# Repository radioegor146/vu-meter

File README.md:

# vu-meter

Physical VU meter for use with rack audio equipment

Consists of:
- 1 processor board
- 4 indicator boards (2 boards per channel)

## Processor board

The processor board is a simple board with converter from balanced input to unbalanced with 
2 x CH32X035F7P6 MCU to convert from analog domain to digital for output to SPI for shift registers.

## Indicator board

This board consists of 5 74HC595D shift registers for 35 individual LEDs.

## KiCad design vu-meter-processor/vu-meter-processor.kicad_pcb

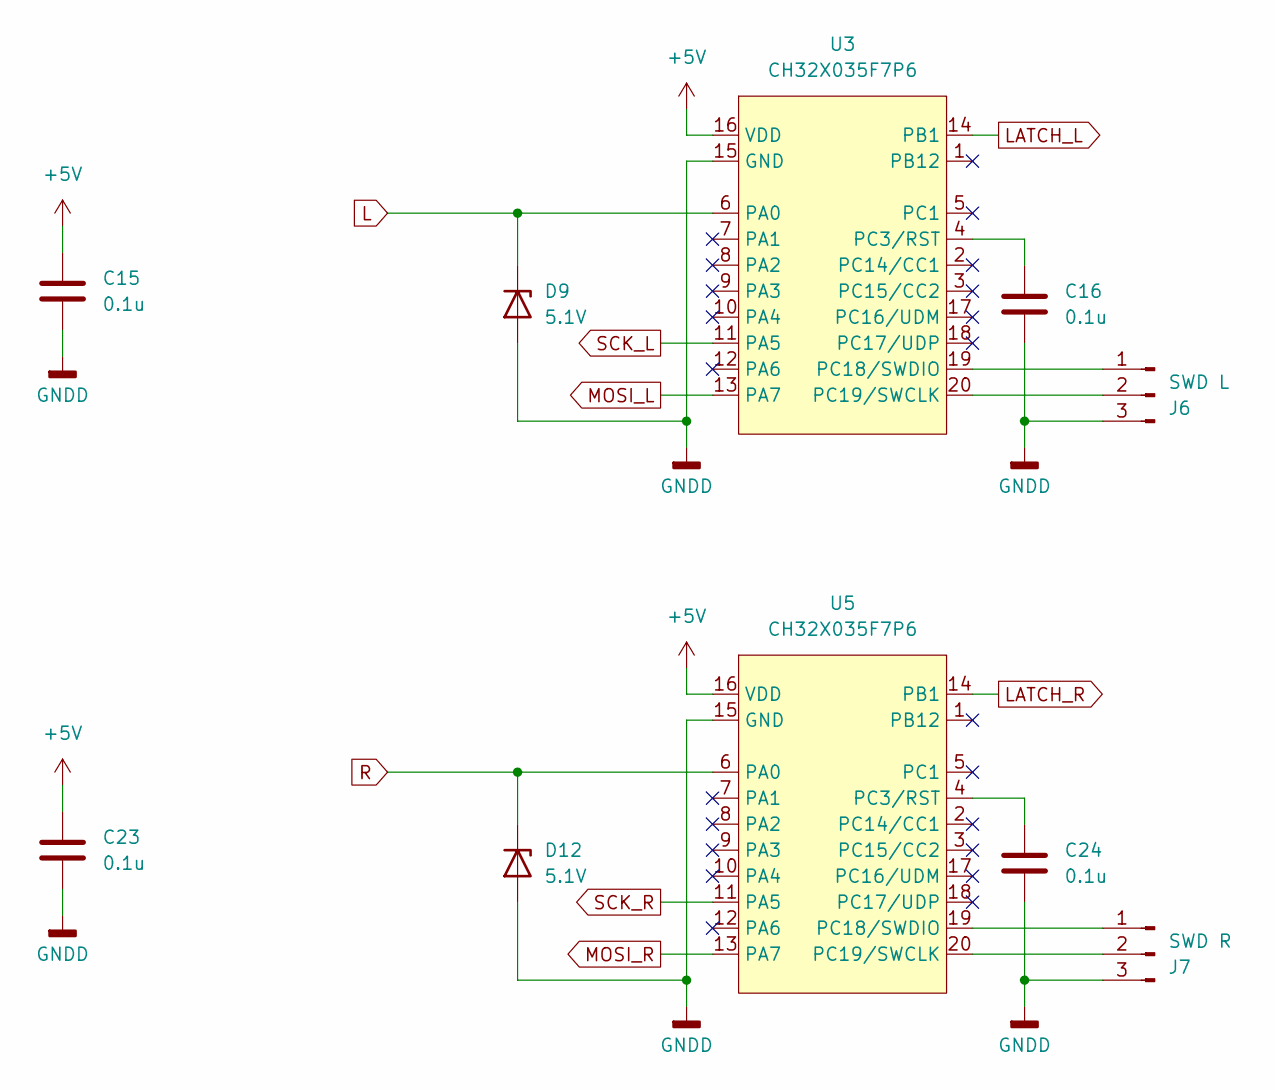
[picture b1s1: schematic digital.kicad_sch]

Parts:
C15, C16, C23, C24: 0.1u; C_0805_2012Metric
D9, D12: 5.1V; D_MiniMELF
J6: SWD L; PinHeader_1x03_P2.54mm_Vertical
J7: SWD R; PinHeader_1x03_P2.54mm_Vertical
U3, U5: CH32X035F7P6; TSSOP-20_4.4x6.5mm_P0.65mm

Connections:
+5V: C15.1, C23.1, U3.16 (VDD), U5.16 (VDD); also elsewhere on the board
GNDA: C15.2, C16.2, C23.2, C24.2, D9.2 (A), D12.2 (A), J6.3, J7.3, U3.15 (GND), U5.15 (GND); also elsewhere on the board
L: D9.1 (K), U3.6 (PA0); also elsewhere on the board
LATCH_L: U3.14 (PB1); also elsewhere on the board
LATCH_R: U5.14 (PB1); also elsewhere on the board
MOSI_L: U3.13 (PA7); also elsewhere on the board
MOSI_R: U5.13 (PA7); also elsewhere on the board
unnamed: J6.1, U3.19 (PC18/SWDIO)
unnamed: J6.2, U3.20 (PC19/SWCLK)
unnamed: J7.1, U5.19 (PC18/SWDIO)
unnamed: J7.2, U5.20 (PC19/SWCLK)
unnamed: C16.1, U3.4 (PC3/RST)
unnamed: C24.1, U5.4 (PC3/RST)
R: D12.1 (K), U5.6 (PA0); also elsewhere on the board
SCK_L: U3.11 (PA5); also elsewhere on the board
SCK_R: U5.11 (PA5); also elsewhere on the board

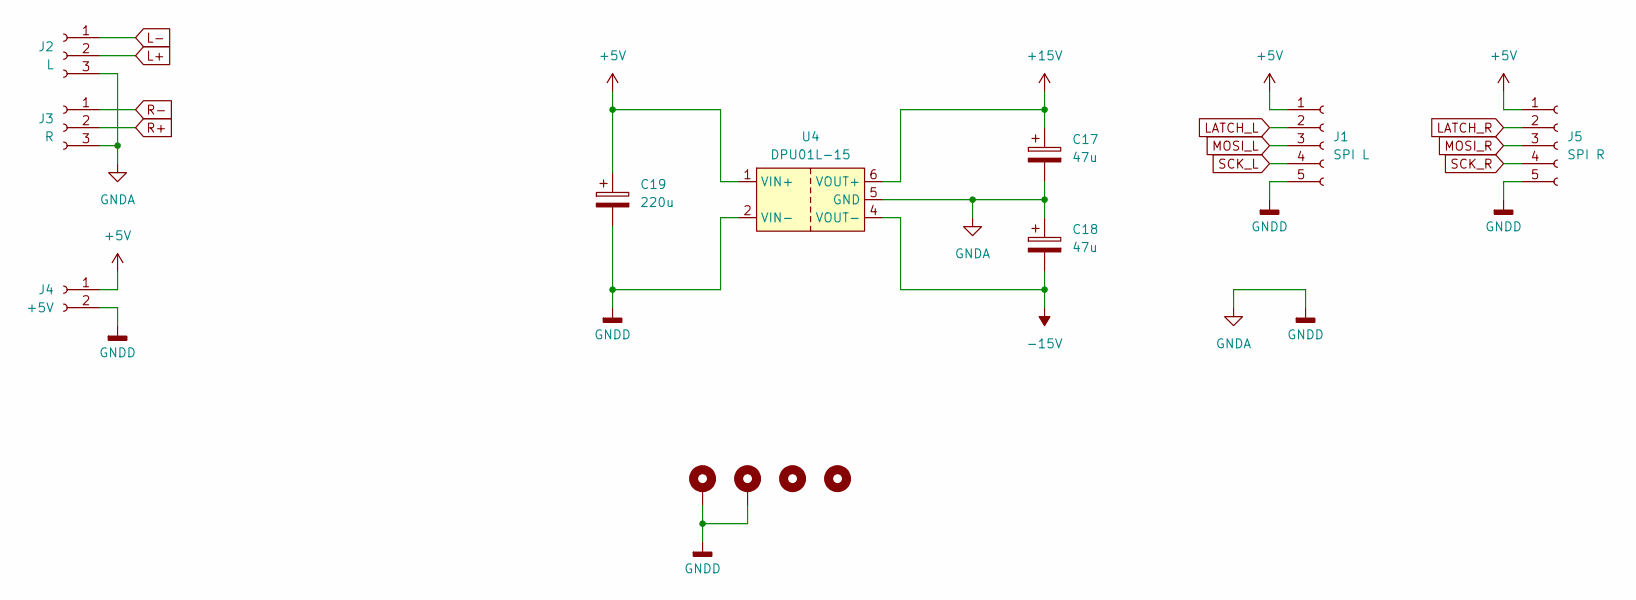
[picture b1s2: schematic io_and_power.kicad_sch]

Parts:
C17, C18: 47u; CP_Radial_D6.3mm_P2.50mm
C19: 220u; CP_Radial_D8.0mm_P3.50mm
H1, H2, H3, H4: MountingHole_Pad; MountingHole_3.2mm_M3_DIN965_Pad_TopOnly
J1: SPI L; JST_XH_B5B-XH-A_1x05_P2.50mm_Vertical
J2: L; JST_XH_B3B-XH-A_1x03_P2.50mm_Vertical
J3: R; JST_XH_B3B-XH-A_1x03_P2.50mm_Vertical
J4: +5V; JST_XH_B2B-XH-A_1x02_P2.50mm_Vertical
J5: SPI R; JST_XH_B5B-XH-A_1x05_P2.50mm_Vertical
U4: DPU01L-15

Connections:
+5V: C19.1, J1.1, J4.1, J5.1, U4.1 (VIN+); also elsewhere on the board
+15V: C17.1, U4.6 (VOUT+); also elsewhere on the board
-15V: C18.2, U4.4 (VOUT-); also elsewhere on the board
GNDA: C17.2, C18.1, C19.2, H1.1, H2.1, J1.5, J2.3, J3.3, J4.2, J5.5, U4.2 (VIN-), U4.5 (GND); also elsewhere on the board
L+: J2.2; also elsewhere on the board
L-: J2.1; also elsewhere on the board
LATCH_L: J1.2; also elsewhere on the board
LATCH_R: J5.2; also elsewhere on the board
MOSI_L: J1.3; also elsewhere on the board
MOSI_R: J5.3; also elsewhere on the board
R+: J3.2; also elsewhere on the board
R-: J3.1; also elsewhere on the board
SCK_L: J1.4; also elsewhere on the board
SCK_R: J5.4; also elsewhere on the board

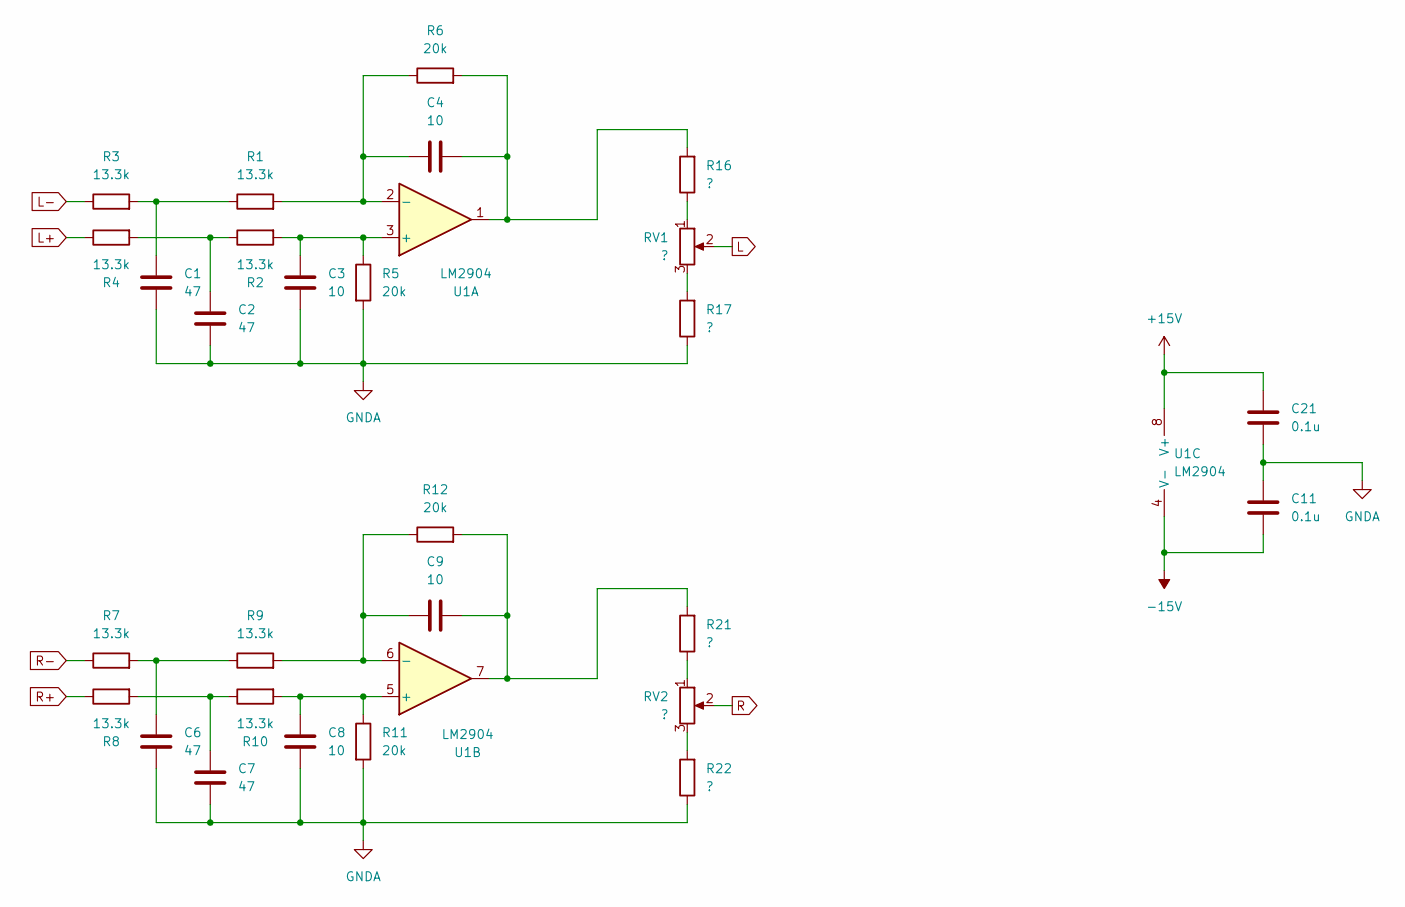
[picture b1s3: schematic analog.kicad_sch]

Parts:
C1, C2, C6, C7: 47; C_0805_2012Metric
C3, C4, C8, C9: 10; C_0805_2012Metric
C11, C21: 0.1u; C_0805_2012Metric
R1, R2, R3, R4, R7, R8, R9, R10: 13.3k; R_0805_2012Metric
R5, R6, R11, R12: 20k; R_0805_2012Metric
R16, R17, R21, R22: ?; R_0805_2012Metric
RV1, RV2: ?; Potentiometer_Bourns_3296W_Vertical
U1: LM2904; SOP-8_3.9x4.9mm_P1.27mm

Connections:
+15V: C21.1, U1.8 (V+); also elsewhere on the board
-15V: C11.2, U1.4 (V-); also elsewhere on the board
GNDA: C1.2, C2.2, C3.2, C6.2, C7.2, C8.2, C11.1, C21.2, R5.2, R11.2, R17.1, R22.1; also elsewhere on the board
L: RV1.2; also elsewhere on the board
L+: R4.1; also elsewhere on the board
L-: R3.1; also elsewhere on the board
unnamed: C1.1, R1.1, R3.2
unnamed: C2.1, R2.1, R4.2
unnamed: C4.2, R6.2, R16.2, U1.1
unnamed: C6.1, R7.2, R9.1
unnamed: C7.1, R8.2, R10.1
unnamed: C9.2, R12.2, R21.2, U1.7
unnamed: R16.1, RV1.1
unnamed: R17.2, RV1.3
unnamed: R21.1, RV2.1
unnamed: R22.2, RV2.3
unnamed: C3.1, R2.2, R5.1, U1.3 (+)
unnamed: C4.1, R1.2, R6.1, U1.2 (-)
unnamed: C8.1, R10.2, R11.1, U1.5 (+)
unnamed: C9.1, R9.2, R12.1, U1.6 (-)
R: RV2.2; also elsewhere on the board
R+: R8.1; also elsewhere on the board
R-: R7.1; also elsewhere on the board

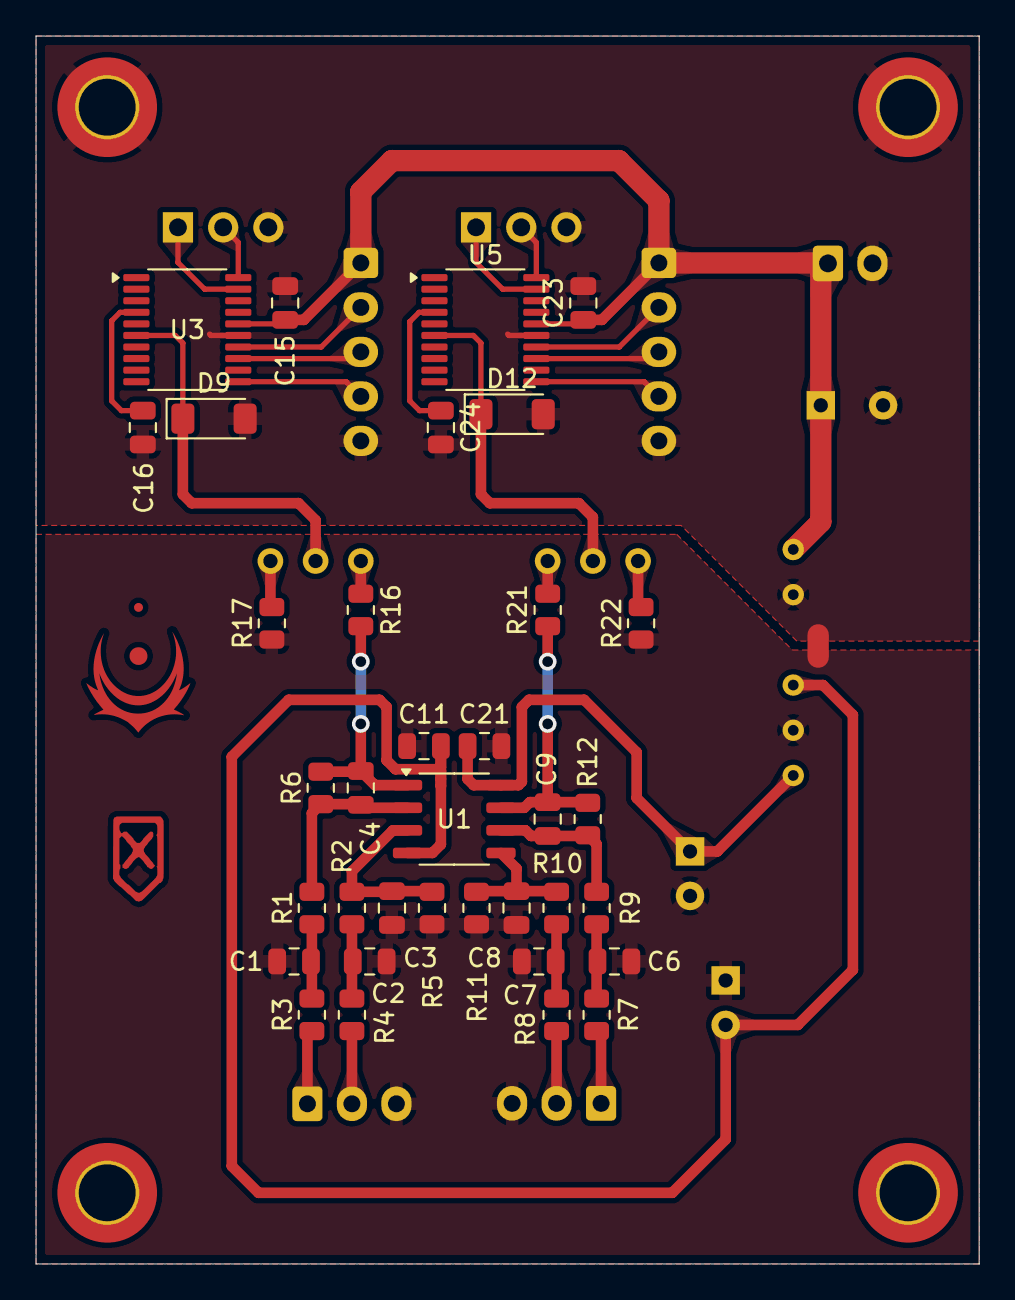
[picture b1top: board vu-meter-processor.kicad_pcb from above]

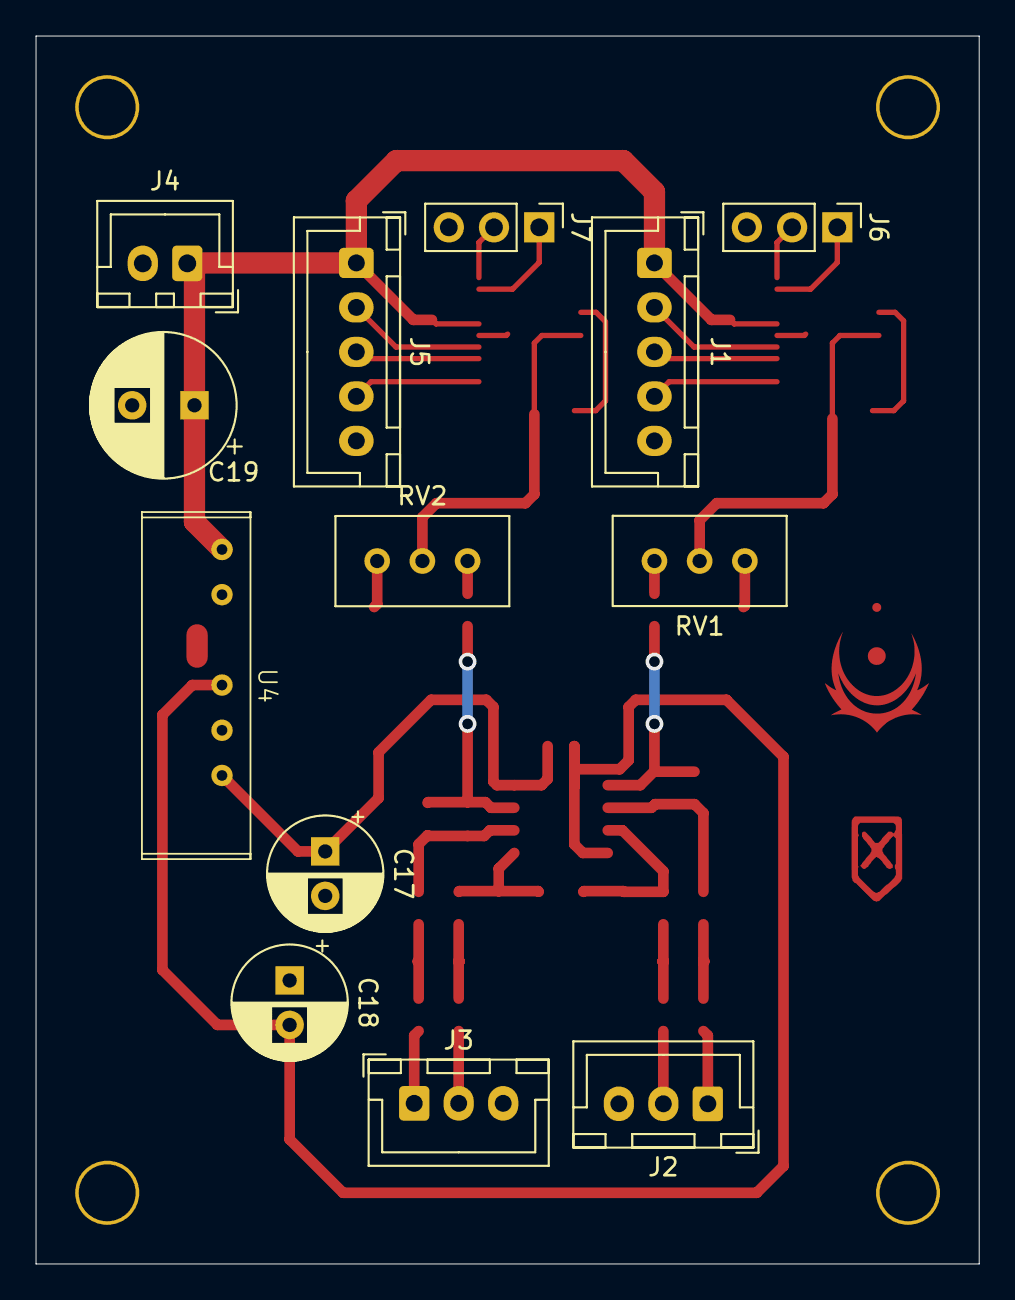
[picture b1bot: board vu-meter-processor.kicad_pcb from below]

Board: 2 copper layers, 53.0 x 69.0 mm, 52 parts (13 on the bottom side), 36 nets.

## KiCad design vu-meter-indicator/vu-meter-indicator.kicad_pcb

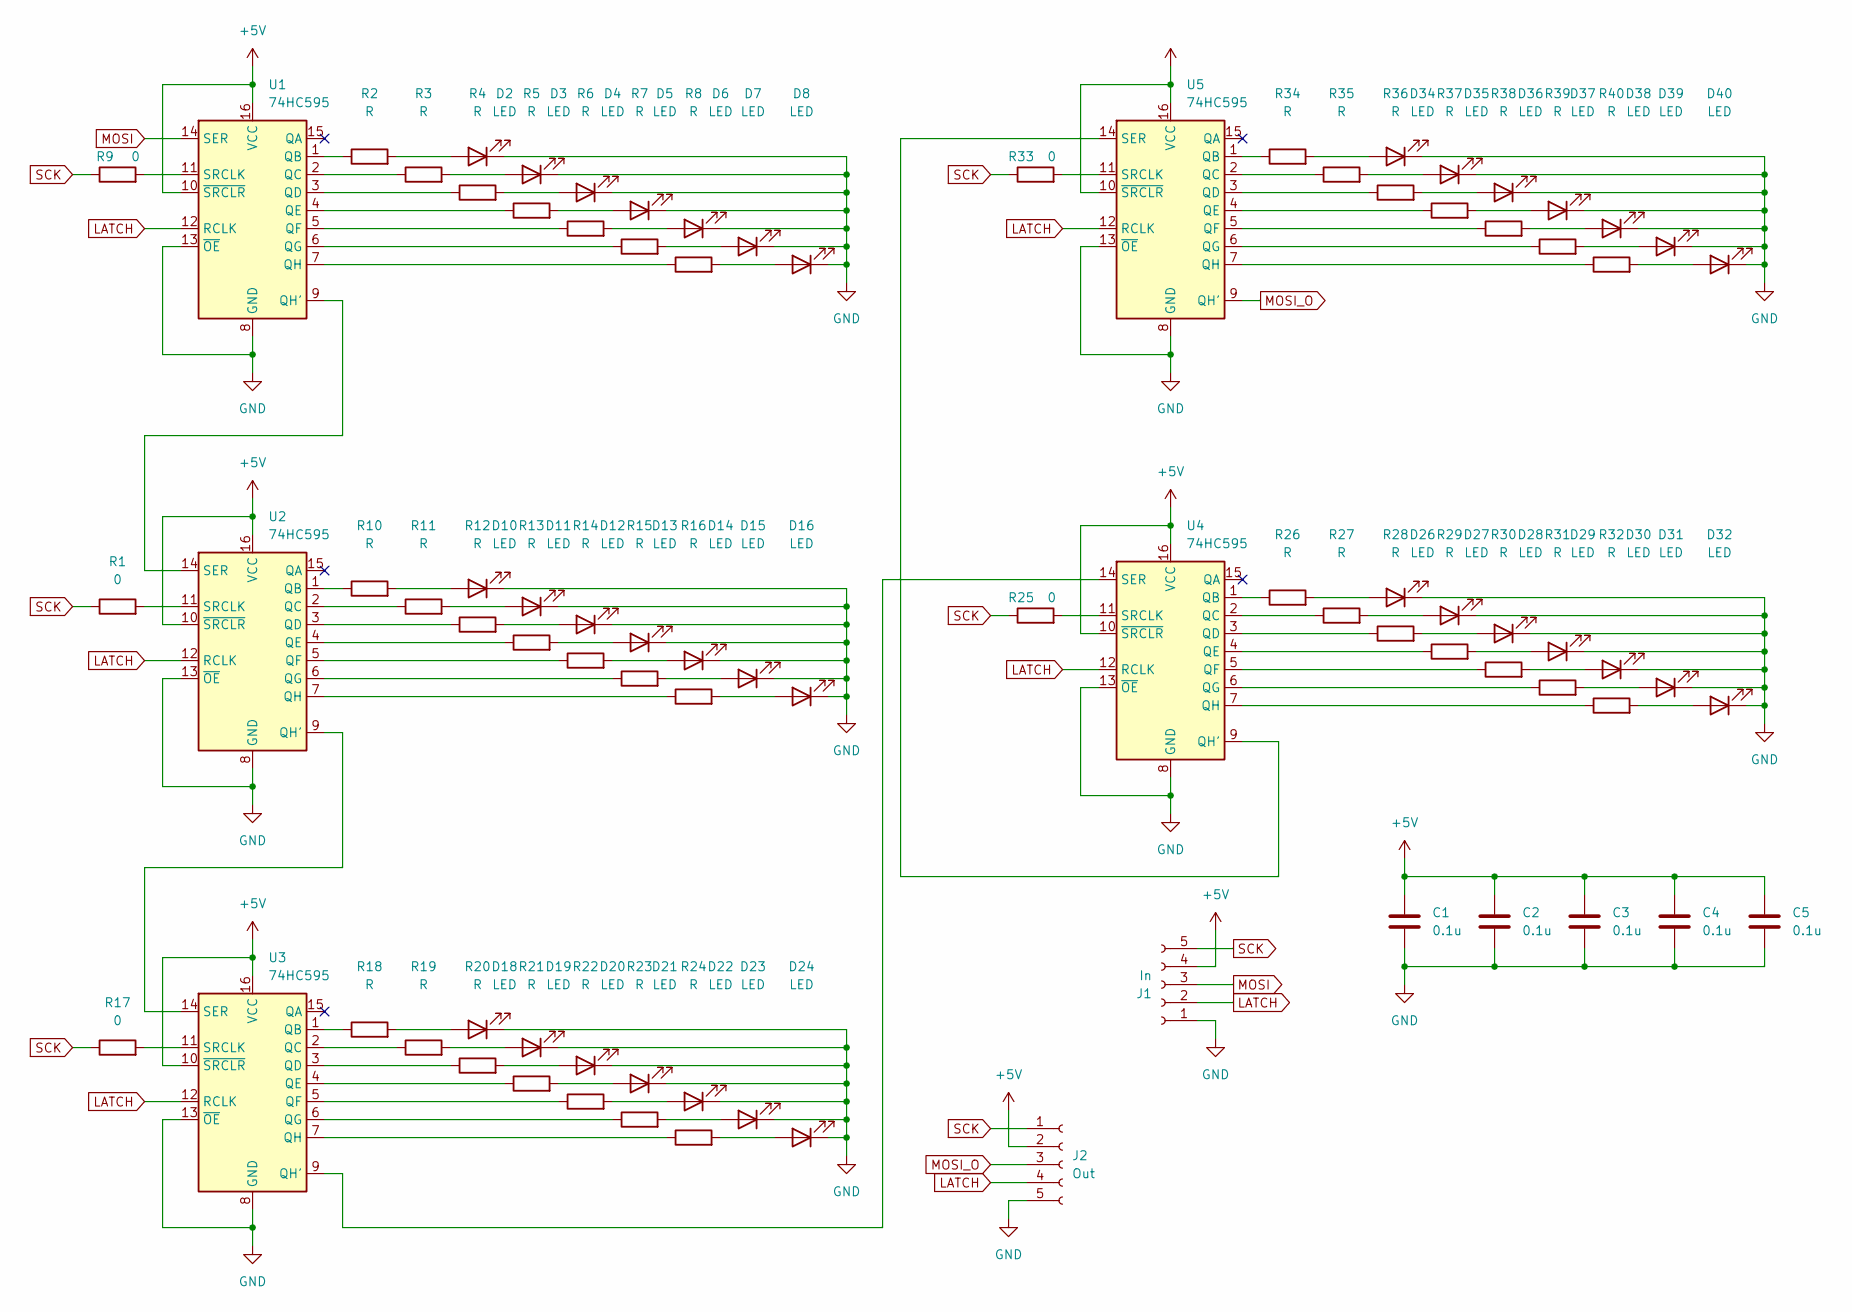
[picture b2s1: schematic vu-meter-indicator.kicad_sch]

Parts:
C1, C2, C3, C4, C5: 0.1u; C_0805_2012Metric
D2, D3, D4, D5, D6, D7, D8, D10, D11, D12, D13, D14, D15, D16, D18, D19, D20, D21, D22, D23, D24, D26, D27, D28, D29, D30, D31, D32, D34, D35, D36, D37, D38, D39, D40: LED
J1: In; SMD_Connector
J2: Out; SMD_Connector
R1, R9, R17, R25, R33: 0; R_1206_3216Metric
R2, R3, R4, R5, R6, R7, R8, R10, R11, R12, R13, R14, R15, R16, R18, R19, R20, R21, R22, R23, R24, R26, R27, R28, R29, R30, R31, R32, R34, R35, R36, R37, R38, R39, R40: R; R_0805_2012Metric
U1, U2, U3, U4, U5: 74HC595; SOP-16_3.9x9.9mm_P1.27mm

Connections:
+5V: C1.1, C2.1, C3.1, C4.1, C5.1, J1.4, J2.2, U1.10 (~SRCLR), U1.16 (VCC), U2.10 (~SRCLR), U2.16 (VCC), U3.10 (~SRCLR), U3.16 (VCC), U4.10 (~SRCLR), U4.16 (VCC), U5.10 (~SRCLR), U5.16 (VCC)
GND: C1.2, C2.2, C3.2, C4.2, C5.2, D2.1 (K), D3.1 (K), D4.1 (K), D5.1 (K), D6.1 (K), D7.1 (K), D8.1 (K), D10.1 (K), D11.1 (K), D12.1 (K), D13.1 (K), D14.1 (K), D15.1 (K), D16.1 (K), D18.1 (K), D19.1 (K), D20.1 (K), D21.1 (K), D22.1 (K), D23.1 (K), D24.1 (K), D26.1 (K), D27.1 (K), D28.1 (K), D29.1 (K), D30.1 (K), D31.1 (K), D32.1 (K), D34.1 (K), D35.1 (K), D36.1 (K), D37.1 (K), D38.1 (K), D39.1 (K), D40.1 (K), J1.1, J2.5, U1.8 (GND), U1.13 (~OE), U2.8 (GND), U2.13 (~OE), U3.8 (GND), U3.13 (~OE), U4.8 (GND), U4.13 (~OE), U5.8 (GND), U5.13 (~OE)
LATCH: J1.2, J2.4, U1.12 (RCLK), U2.12 (RCLK), U3.12 (RCLK), U4.12 (RCLK), U5.12 (RCLK)
MOSI: J1.3, U1.14 (SER)
MOSI_O: J2.3, U5.9 (QH')
unnamed: D2.2 (A), R2.2
unnamed: D3.2 (A), R3.2
unnamed: D4.2 (A), R4.2
unnamed: D5.2 (A), R5.2
unnamed: D6.2 (A), R6.2
unnamed: D7.2 (A), R7.2
unnamed: D8.2 (A), R8.2
unnamed: D10.2 (A), R10.2
unnamed: D11.2 (A), R11.2
unnamed: D12.2 (A), R12.2
unnamed: D13.2 (A), R13.2
unnamed: D14.2 (A), R14.2
unnamed: D15.2 (A), R15.2
unnamed: D16.2 (A), R16.2
unnamed: D18.2 (A), R18.2
unnamed: D19.2 (A), R19.2
unnamed: D20.2 (A), R20.2
unnamed: D21.2 (A), R21.2
unnamed: D22.2 (A), R22.2
unnamed: D23.2 (A), R23.2
unnamed: D24.2 (A), R24.2
unnamed: D26.2 (A), R26.2
unnamed: D27.2 (A), R27.2
unnamed: D28.2 (A), R28.2
unnamed: D29.2 (A), R29.2
unnamed: D30.2 (A), R30.2
unnamed: D31.2 (A), R31.2
unnamed: D32.2 (A), R32.2
unnamed: D34.2 (A), R34.2
unnamed: D35.2 (A), R35.2
unnamed: D36.2 (A), R36.2
unnamed: D37.2 (A), R37.2
unnamed: D38.2 (A), R38.2
unnamed: D39.2 (A), R39.2
unnamed: D40.2 (A), R40.2
unnamed: R2.1, U1.1 (QB)
unnamed: R3.1, U1.2 (QC)
unnamed: R4.1, U1.3 (QD)
unnamed: R5.1, U1.4 (QE)
unnamed: R6.1, U1.5 (QF)
unnamed: R7.1, U1.6 (QG)
unnamed: U1.9 (QH'), U2.14 (SER)
unnamed: R8.1, U1.7 (QH)
unnamed: R9.2, U1.11 (SRCLK)
unnamed: R10.1, U2.1 (QB)
unnamed: R11.1, U2.2 (QC)
unnamed: R12.1, U2.3 (QD)
unnamed: R13.1, U2.4 (QE)
unnamed: R14.1, U2.5 (QF)
unnamed: R15.1, U2.6 (QG)
unnamed: U2.9 (QH'), U3.14 (SER)
unnamed: R16.1, U2.7 (QH)
unnamed: R1.2, U2.11 (SRCLK)
unnamed: R18.1, U3.1 (QB)
unnamed: R19.1, U3.2 (QC)
unnamed: R20.1, U3.3 (QD)
unnamed: R21.1, U3.4 (QE)
unnamed: R22.1, U3.5 (QF)
unnamed: R23.1, U3.6 (QG)
unnamed: U3.9 (QH'), U4.14 (SER)
unnamed: R24.1, U3.7 (QH)
unnamed: R17.2, U3.11 (SRCLK)
unnamed: R26.1, U4.1 (QB)
unnamed: R27.1, U4.2 (QC)
unnamed: R28.1, U4.3 (QD)
unnamed: R29.1, U4.4 (QE)
unnamed: R30.1, U4.5 (QF)
unnamed: R31.1, U4.6 (QG)
unnamed: U4.9 (QH'), U5.14 (SER)
unnamed: R32.1, U4.7 (QH)
unnamed: R25.2, U4.11 (SRCLK)
unnamed: R34.1, U5.1 (QB)
unnamed: R35.1, U5.2 (QC)
unnamed: R36.1, U5.3 (QD)
unnamed: R37.1, U5.4 (QE)
unnamed: R38.1, U5.5 (QF)
unnamed: R39.1, U5.6 (QG)
unnamed: R40.1, U5.7 (QH)
unnamed: R33.2, U5.11 (SRCLK)
SCK: J1.5, J2.1, R1.1, R9.1, R17.1, R25.1, R33.1

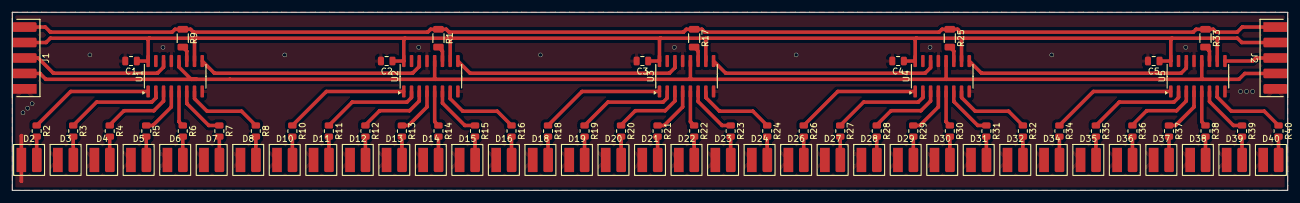
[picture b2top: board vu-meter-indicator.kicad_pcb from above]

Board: 2 copper layers, 209.5 x 29.2 mm, 87 parts (0 on the bottom side), 85 nets.

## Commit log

2025-06-18 main commit
2025-06-18 add pdfs for schematic and pcbs
2025-06-22 fix: change overall power supply to only 5V, make peak detector DNP for now
2025-06-22 add: front panel drawings
2025-06-23 remove analog peak detector fully and split one chip into two for better inter-channel performance
2025-07-03 fix: remove dc blocking capacitors
